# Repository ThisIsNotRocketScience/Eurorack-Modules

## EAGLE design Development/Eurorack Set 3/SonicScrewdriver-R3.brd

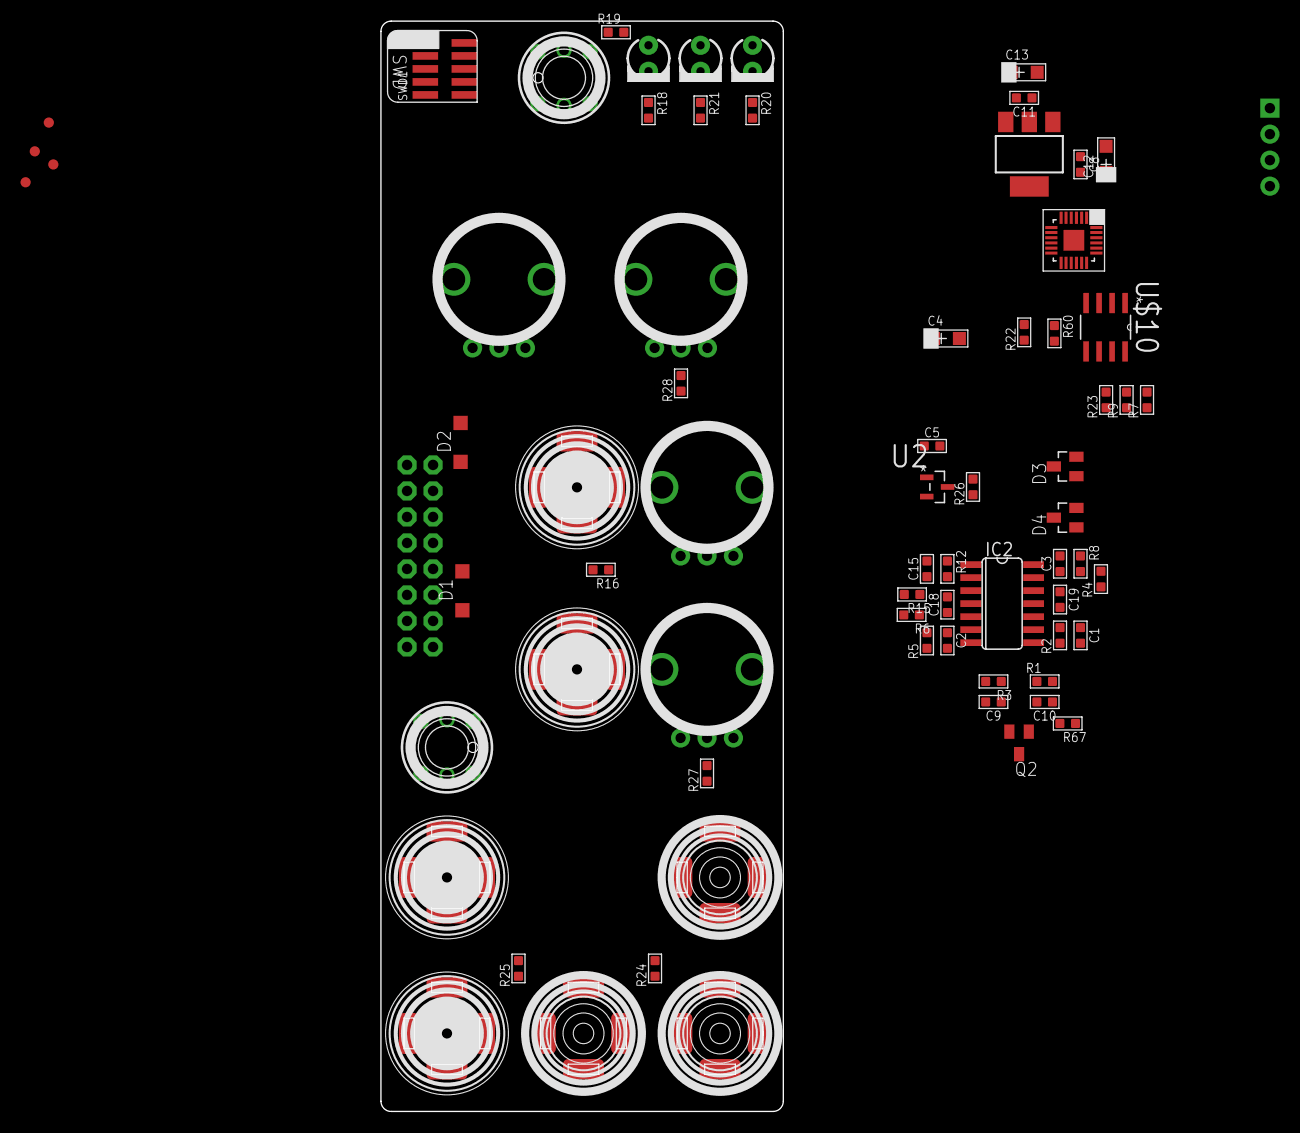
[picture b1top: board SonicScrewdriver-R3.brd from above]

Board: 2 copper layers, 39.3 x 106.5 mm, 73 parts (1 on the bottom side), 49 nets, no tracks yet.

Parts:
C1, C2, C3, C15: 3.3n; C0603
C4, C12: 10uF; AVX-A
C5, C9: 1uF; C0603
C8, C10, C18, C19: 100nF; C0603
C11: 100Nf; C0603
C13: 10Uf; AVX-A
D1, D2: 1N5819HW; SOD123
D3, D4: BAS70-04; SOT23
GATE, GATE1: Gate; 3.5MM-JACK-SWITCH-13MM-INPUT
IC1: LD1117AS33TR; SOT223
IC2: MCP6004; SO14
IN1: In 2; 3.5MM-JACK-SWITCH-13MM-INPUT
IN2: In 1; 3.5MM-JACK-SWITCH-13MM-INPUT
JP1: 1X04
LED1, LED2, LED3: LED3MM
Q2: MMBT3904; SOT23-BEC
R1, R3, R4, R5, R6, R8, R15, R16, R26, R27, R28, R67: 100k; R0603
R2, R7, R9, R12: 33k; R0603
R13: A; OG-POTS_ALPS_POT_VERTICAL
R14: D; OG-POTS_ALPS_POT_VERTICAL
R17: B; OG-POTS_ALPS_POT_VERTICAL
R18, R20, R21: 2k; R0603
R19, R22: 56; R0603
R23, R60: 10k; R0603
R24, R25: 51; R0603
R90: C; OG-POTS_ALPS_POT_VERTICAL
SWD1: CORTEX_SWD; M50-3600542
U1: MKL02Z32VFK4; QFN50P400X400X100-25N
U2: LM4040DIM3-5.0; SOT95P237X112-3N
U$1: POWER; POWER_16
U$2: EURORACK_PCB8HP; EURORACK8HPPCB
U$3, U$6: SWITCH_W_LED_PB6149L-X-102WHITE; PB6149L
U$4, U$5, U$9, U$11: FIDUCIAL; FIDUCIAL_1MM
U$7: Out 2; 3.5MM-JACK-SWITCH-13MM-OUTPUT
U$8, U$12: Out 1; 3.5MM-JACK-SWITCH-13MM-OUTPUT
U$10: MCP4822-E/SN; SOIC8-N_MC

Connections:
3.3V: C8.2, C9.2, C10.2, C12.+, D3.2, D4.2, IC1.2, IC1.4, JP1.4, R13.P$3, R14.P$3, R17.P$3, R23.2, R60.2, R90.P$3, SWD1.1, U1.3, U$3.LEDPOS, U$10.1
ADC_1: C15.2, D3.3, IC2.1, R12.1, U1.15
ADC_2: C1.2, D4.3, IC2.8, R2.1, U1.16
DACCS: U1.7, U$10.2
DACSCK: U1.12, U$10.3
DACSDI: U1.11, U$10.4
GATE: Q2.C, R60.1, U1.8
GND: C4.+, C5.1, C8.1, C9.1, C10.1, C11.1, C12.-, C13.-, C18.1, C19.1, D3.1, D4.1, GATE.RING@1, GATE.RING@2, IC1.1, IC2.3, IC2.5, IC2.10, IC2.12, IN1.RING@1, IN1.RING@2, IN2.RING@1, IN2.RING@2, JP1.1, Q2.E, R13.P$1, R14.P$1, R17.P$1, R18.2, R19.2, R20.2, R21.2, R90.P$1, SWD1.3, SWD1.5, U1.4, U1.25, U2.1, U$1.3, U$1.4, U$1.5, U$1.6, U$1.7, U$1.8, U$3.3, U$3.4, U$6.3, U$6.4, U$7.RING@1, U$7.RING@2, U$8.RING@1, U$8.RING@2, U$10.5, U$10.7
KNOB_A: R90.P$2, U1.19
KNOB_B: R13.P$2, U1.9
KNOB_C: R14.P$2, R27.2
KNOB_D: R17.P$2, R28.2
LED1: U1.1, U$6.LEDPOS
LED2: LED1.A, U1.20
LED3: LED2.A, U1.14
LED4: LED3.A, U1.13
unnamed: JP1.3, U1.5
unnamed: JP1.2, U1.6
unnamed: IN1.TIP@1, IN1.TIP@2, R16.2
unnamed: C15.1, IC2.2, R12.2, R15.1, R16.1, R27.1
unnamed: SWD1.4, U1.22
unnamed: IN2.TIP@1, IN2.TIP@2, R1.2
unnamed: SWD1.2, U1.24
unnamed: C1.1, IC2.9, R1.1, R2.2, R3.1, R28.1
unnamed: C2.1, IC2.6, R5.2, R6.1, R9.1
unnamed: C3.1, IC2.13, R4.2, R7.1, R8.2
unnamed: R7.2, U$10.8
unnamed: R9.2, U$10.6
unnamed: D1.A, U$1.9, U$1.10
unnamed: R19.1, U$6.LEDNEG
unnamed: LED3.K, R18.1
unnamed: LED2.K, R20.1
unnamed: LED1.K, R21.1
unnamed: C3.2, IC2.14, R8.1, R24.2
unnamed: R22.1, U$3.LEDNEG
unnamed: R25.1, U$8.TIP@1, U$8.TIP@2
unnamed: R24.1, U$7.TIP@1, U$7.TIP@2
unnamed: C2.2, IC2.7, R5.1, R25.2
unnamed: GATE.TIP@1, GATE.TIP@2, R67.1
unnamed: D2.C, U$1.1, U$1.2
unnamed: Q2.B, R67.2
PTA1: SWD1.10, U1.23
RACK_GATE: GATE.SWITCH@1, GATE.SWITCH@2, U$1.15, U$1.16
REF_-5V: C5.2, R3.2, R4.1, R6.2, R15.2, R26.2, U2.2
SW1: U1.2, U$6.1, U$6.2
SW2: R23.1, U1.17, U$3.1, U$3.2
SW2LED: R22.2, U1.18
VEE: C4.-, C19.2, D2.A, IC2.11, R26.1
VIN: C11.2, C13.+, C18.2, D1.C, IC1.3, IC2.4

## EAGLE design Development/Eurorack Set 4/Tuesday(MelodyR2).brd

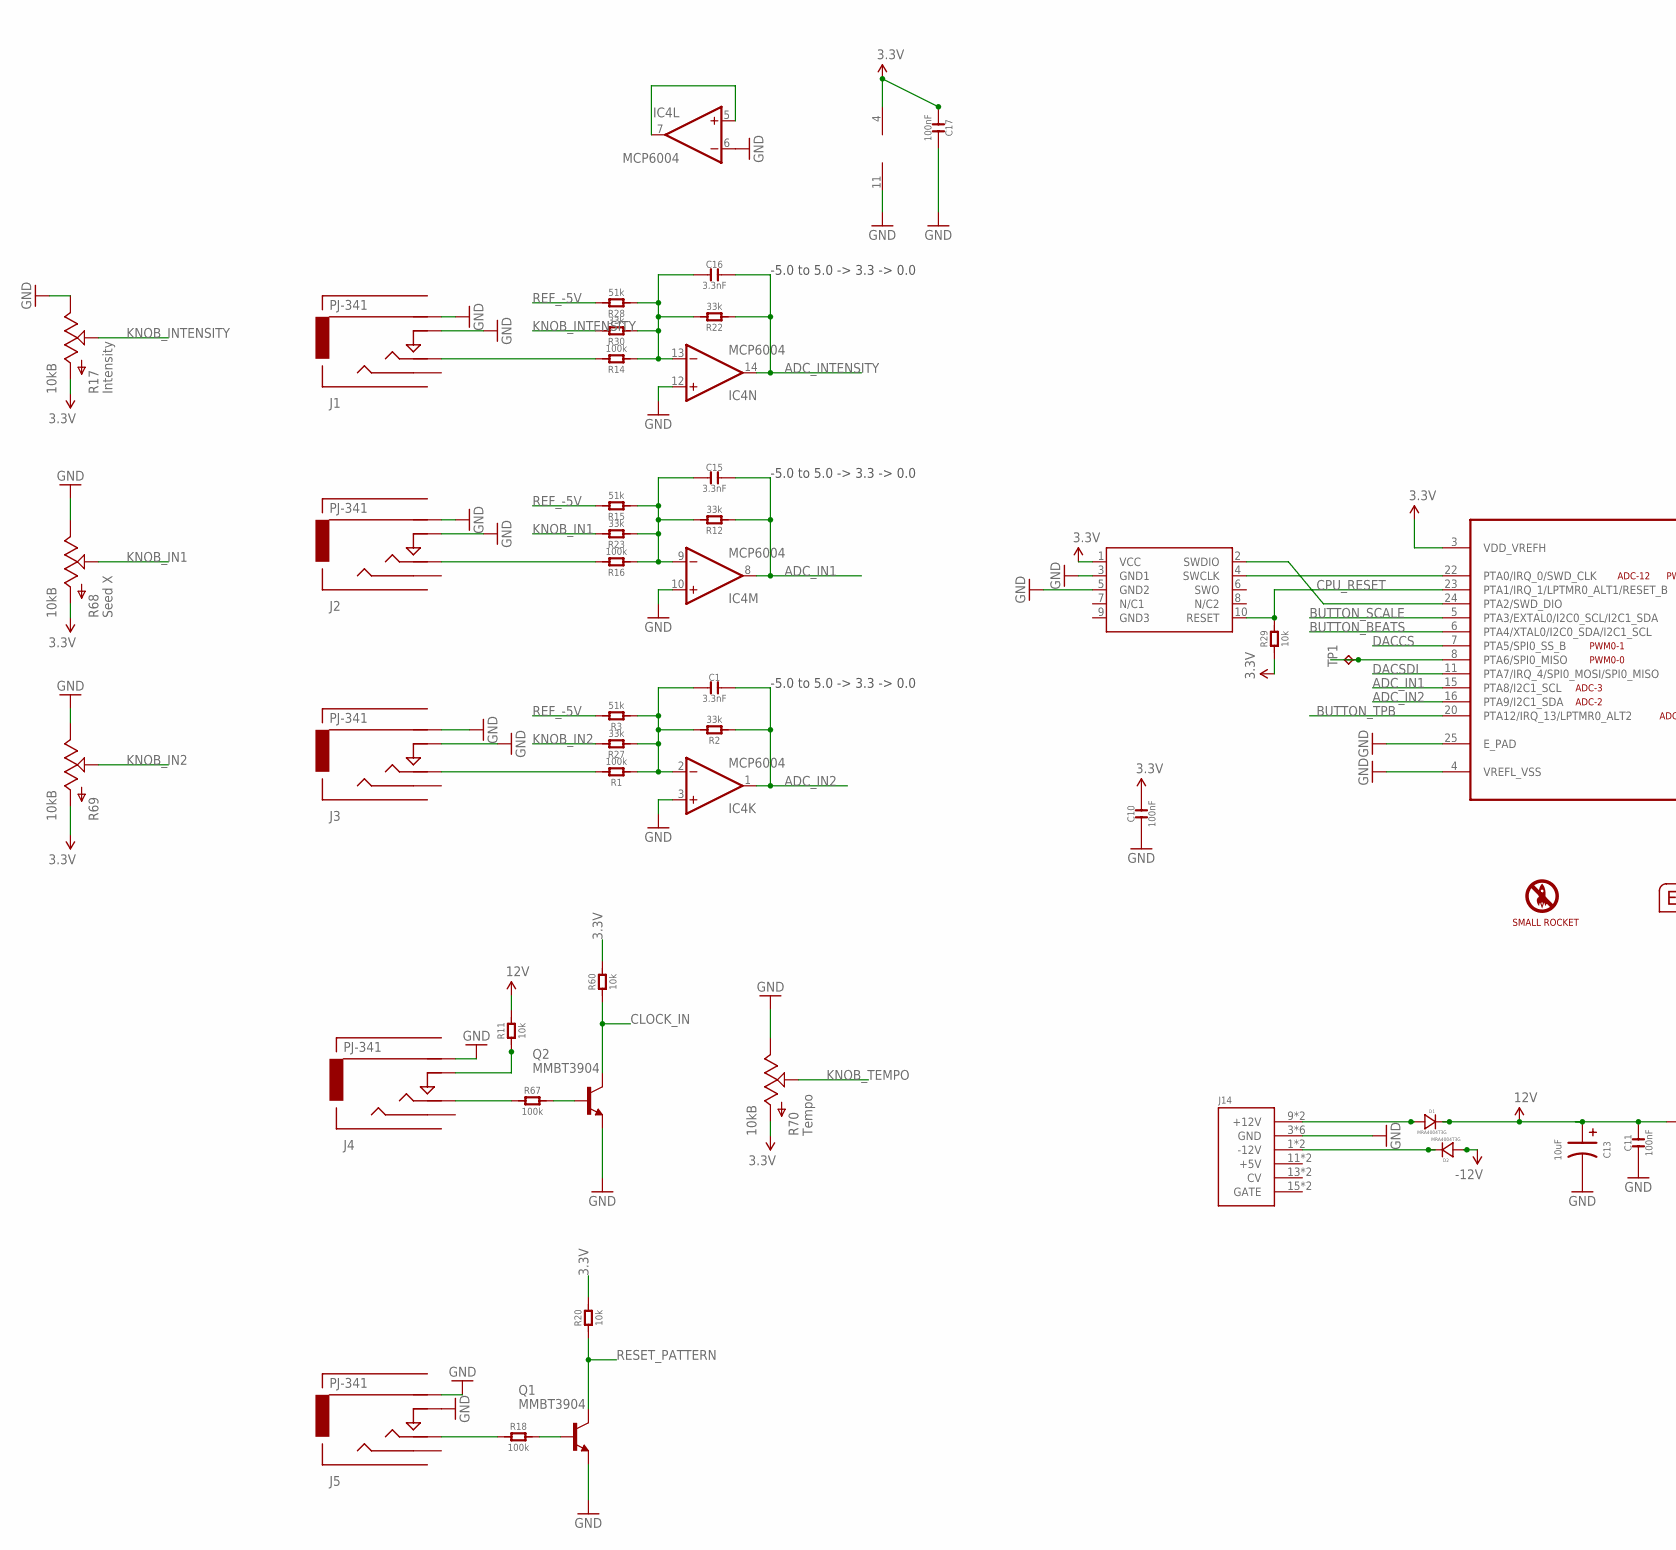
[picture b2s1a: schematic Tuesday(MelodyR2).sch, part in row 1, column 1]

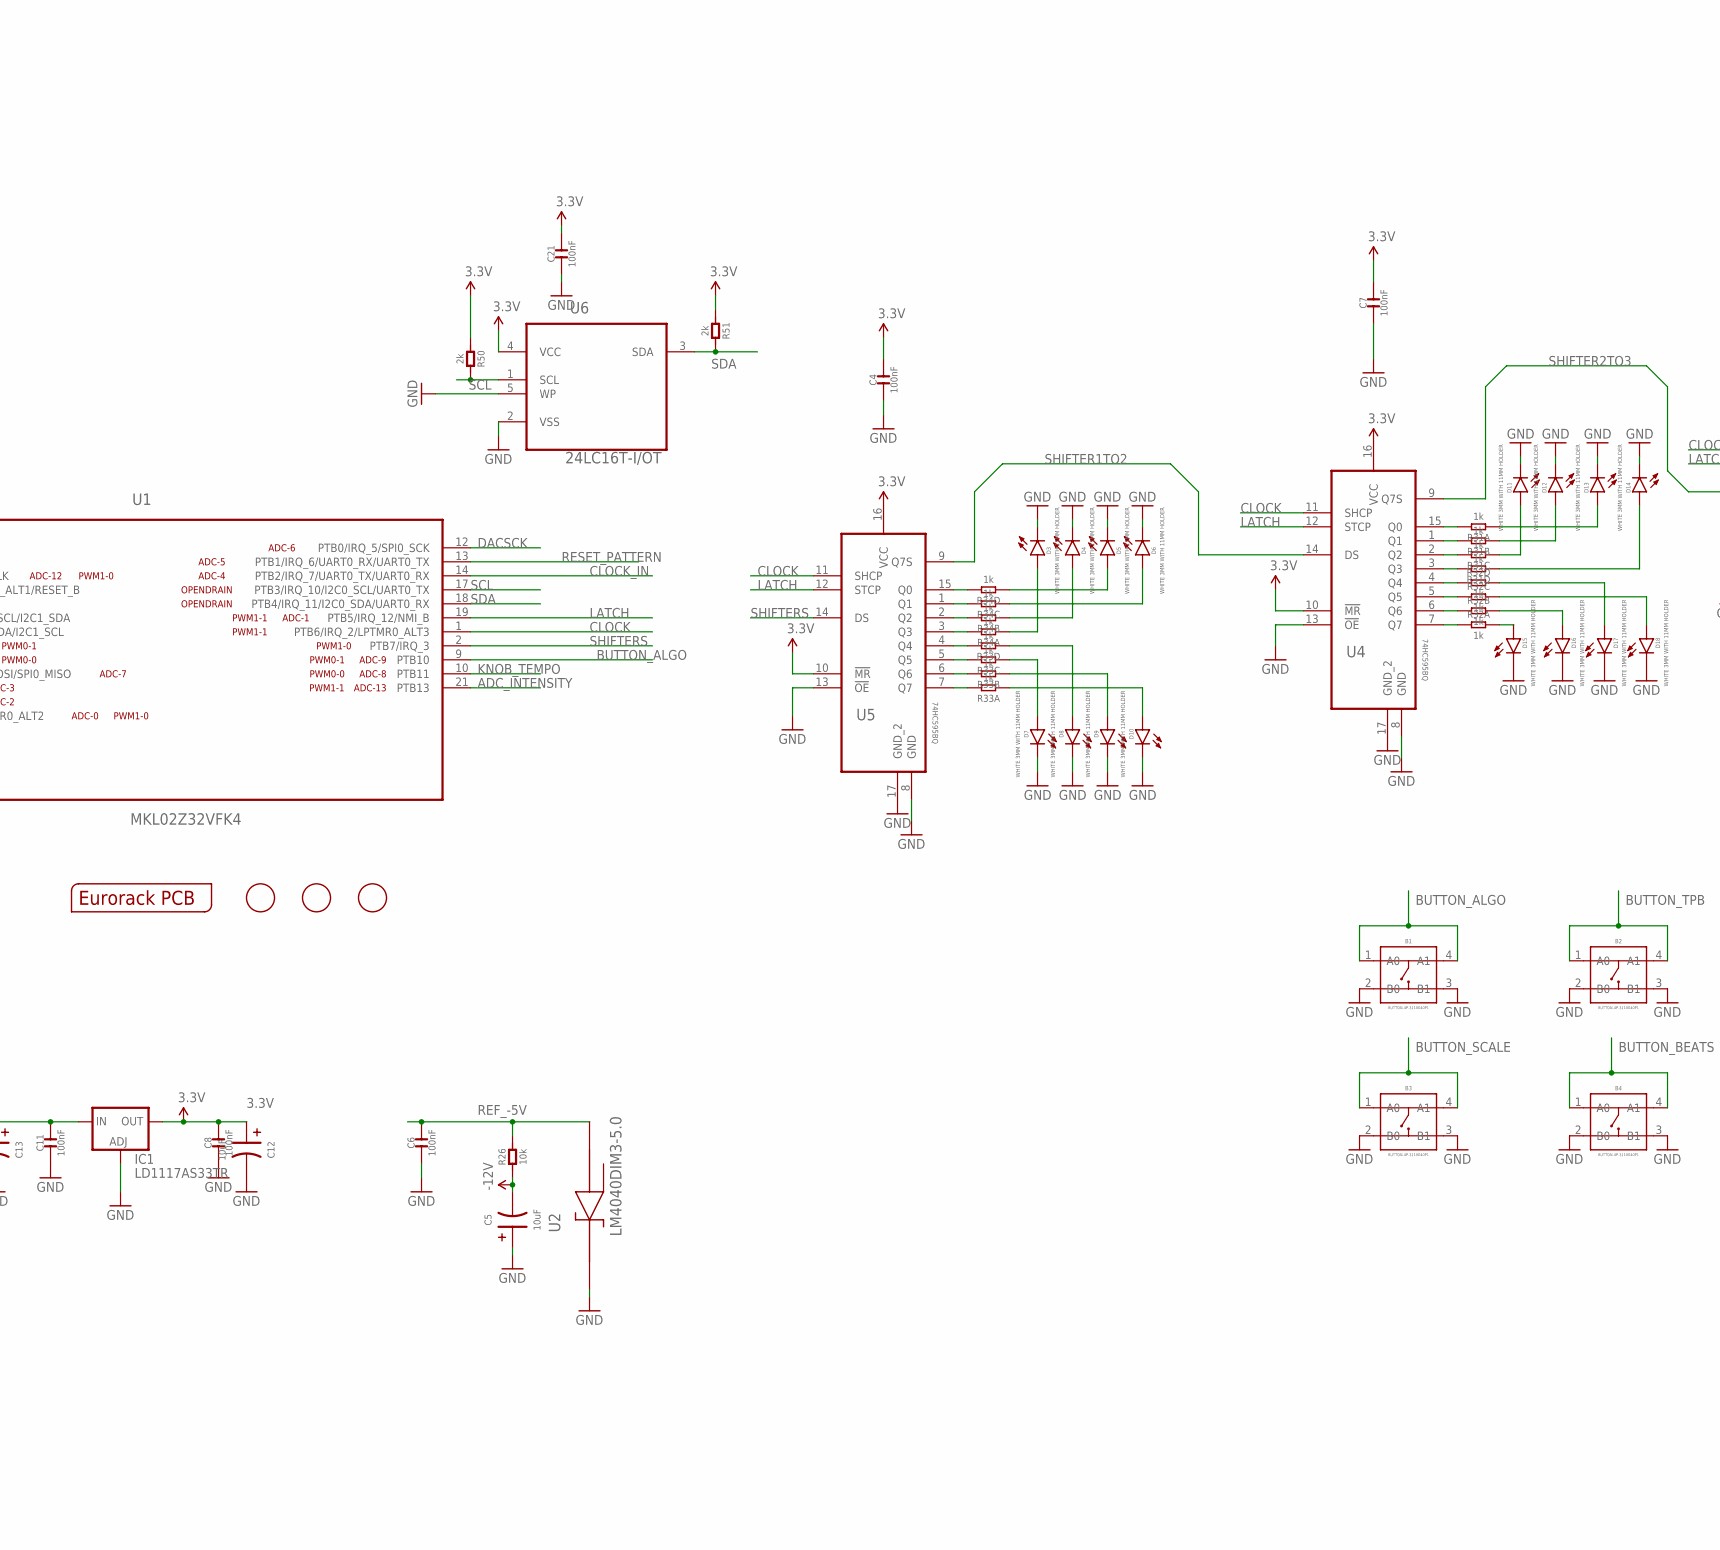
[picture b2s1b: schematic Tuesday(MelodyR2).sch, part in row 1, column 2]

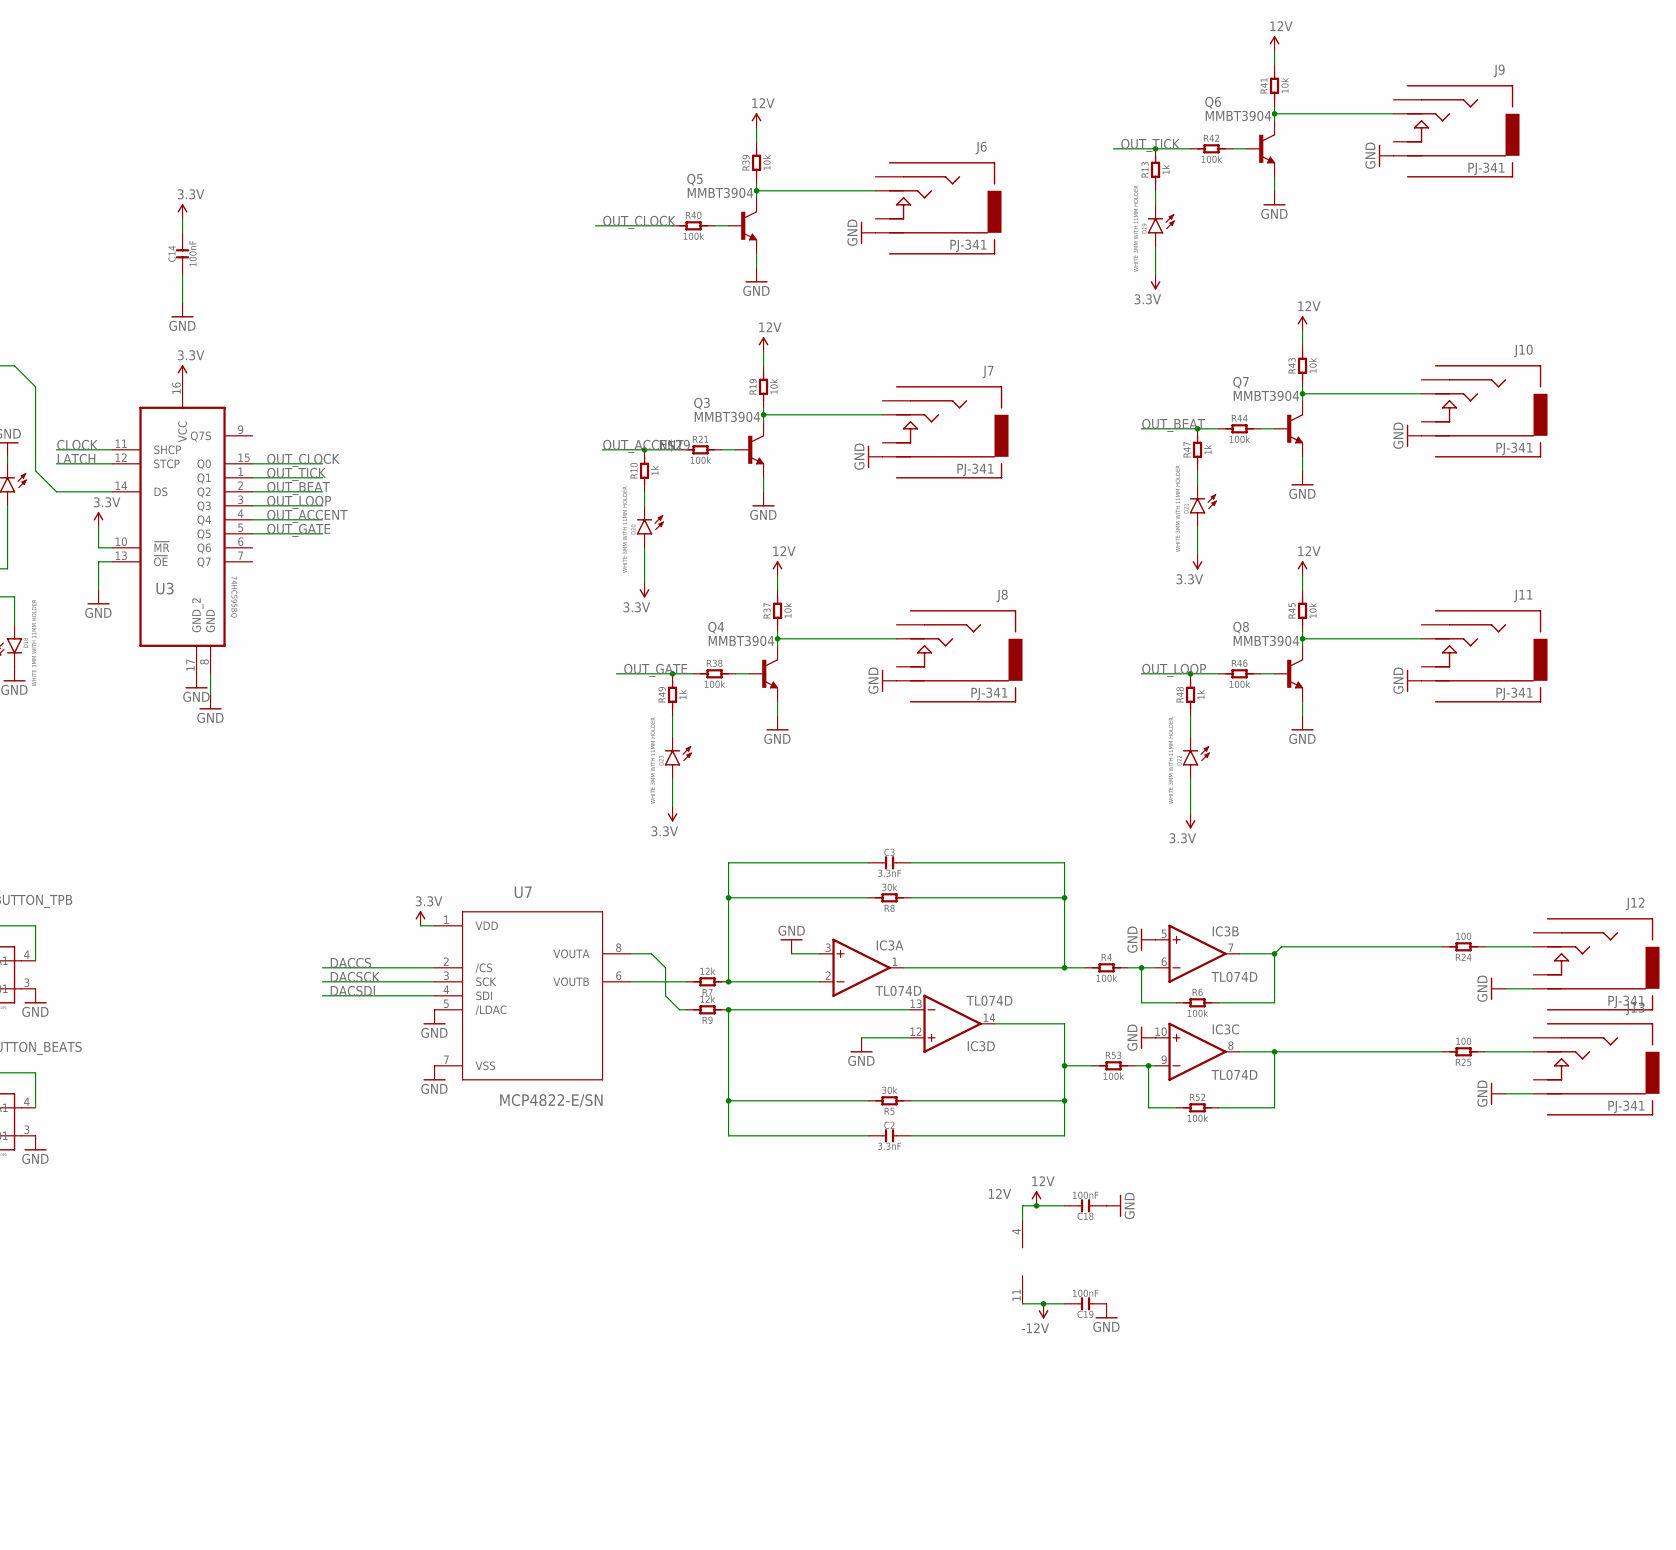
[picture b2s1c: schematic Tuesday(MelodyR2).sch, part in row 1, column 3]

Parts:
B1, B2, B3, B4: BUTTON-4P-3110040P1; 4P-6.0X6.0X5.0H
C1, C2, C3, C15, C16: 3.3nF; C0603
C4, C7, C8, C10, C11, C14, C17, C18, C19, C21: 100nF; C0603; MPN MC0603F104Z160CT
C5, C12, C13: 10uF; AVX-A; MPN TAJB106K020RNJ
C6: 100nF; C0603; MPN 06035C104KAT2A
D1, D2: MRA4004T3G; DO-214AC; MPN US1G-E3/5AT
D3, D4, D5, D6, D7, D8, D9, D10, D11, D12, D13, D14, D15, D16, D17, D18, D19, D20, D21, D22, D23: WHITE 3MM WITH 11MM HOLDER; LED3MM
FID1, FID2, FID3: FIDUCIAL; FIDUCIAL_1MM
IC1: LD1117AS33TR; SOT223; MPN LD1117AS33TR
IC3: TL074D; SO14; MPN TL074CD
IC4: MCP6004; SO14; MPN MCP6004-I/SL.
J1, J2, J3, J4, J5: PJ-341; 3.5MM-JACK-SWITCH-13MM-INPUT
J6, J7, J8, J9, J10, J11, J12, J13: PJ-341; 3.5MM-JACK-SWITCH-13MM-OUTPUT
J14: POWER; POWER_16
OUTLINE: EURORACK_PCB12HP; EURORACK12HPPCB
PRETTY1: SMALLROCKET
Q1, Q2, Q3, Q4, Q5, Q6, Q7, Q8: MMBT3904; SOT23-BEC; MPN PMBT3904,215
R1, R4, R6, R14, R16, R18, R21, R38, R40, R42, R44, R46, R52, R53, R67: 100k; R0603
R2, R12, R22, R23, R27, R30: 33k; R0603
R3, R15, R28: 51k; R0603
R5, R8: 30k; R0603
R7, R9: 12k; R0603
R10, R13, R47, R48, R49: 1k; R0603
R11, R19, R20, R26, R29, R37, R39, R41, R43, R45, R60: 10k; R0603
R17, R68, R69, R70: 10kB; OG-POTS_ALPS_POT_VERTICAL
R24, R25: 100; R0603
R31, R32, R33, R34: 1k; R1206-8
R50, R51: 2k; R0603
SWD1: CORTEX_SWD; M50-3600542
TP1: TPB1,27; B1,27
U1: MKL02Z32VFK4; QFN50P400X400X100-25N
U2: LM4040DIM3-5.0; SOT95P237X112-3N
U3, U4, U5: 74HC595BQ; QFN50P250X350X100-17N
U6: 24LC16T-I/OT; SOT95P290X145-5N; MPN 24LC00T-I/OT
U7: MCP4822-E/SN; SOIC8-N_MC

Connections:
3.3V: C4.2, C7.2, C8.2, C10.2, C12.+ (1), C14.2, C17.1, C21.2, D19.A, D20.A, D21.A, D22.A, D23.A, IC1.2 (OUT), IC1.4 (OUT), IC4.4 (V+), R17.P$3 (A), R20.2, R29.1, R50.1, R51.1, R60.2, R68.P$3 (A), R69.P$3 (A), R70.P$3 (A), SWD1.1 (VCC), U1.3 (VDD_VREFH), U3.10 (!MR), U3.16 (VCC), U4.10 (!MR), U4.16 (VCC), U5.10 (!MR), U5.16 (VCC), U6.4 (VCC), U7.1 (VDD)
12V: C11.2, C13.+ (1), C18.2, D1.2 (-), IC1.3 (IN), IC3.4 (V+), R11.2, R19.2, R37.2, R39.2, R41.2, R43.2, R45.2
-12V: C5.- (2), C19.2, D2.1 (+), IC3.11 (V-), R26.1
ADC_IN1: C15.2, IC4.8 (OUT), R12.1, U1.15 (PTA8/I2C1_SCL)
ADC_IN2: C1.2, IC4.1 (OUT), R2.1, U1.16 (PTA9/I2C1_SDA)
ADC_INTENSITY: C16.2, IC4.14 (OUT), R22.1, U1.21 (PTB13)
BUTTON_ALGO: B1.1 (A0), B1.4 (A1), U1.9 (PTB10)
BUTTON_BEATS: B4.1 (A0), B4.4 (A1), U1.6 (PTA4/XTAL0/I2C0_SDA/I2C1_SCL)
BUTTON_SCALE: B3.1 (A0), B3.4 (A1), U1.5 (PTA3/EXTAL0/I2C0_SCL/I2C1_SDA)
BUTTON_TPB: B2.1 (A0), B2.4 (A1), U1.20 (PTA12/IRQ_13/LPTMR0_ALT2)
CLOCK: U1.1 (PTB6/IRQ_2/LPTMR0_ALT3), U3.11 (SHCP), U4.11 (SHCP), U5.11 (SHCP)
CLOCK_IN: Q2.C, R60.1, U1.14 (PTB2/IRQ_7/UART0_TX/UART0_RX)
CPU_RESET: R29.2, SWD1.10 (RESET), U1.23 (PTA1/IRQ_1/LPTMR0_ALT1/RESET_B)
D21: D21.K (C), R47.1
DACCS: U1.7 (PTA5/SPI0_SS_B), U7.2 (/CS)
DACSCK: U1.12 (PTB0/IRQ_5/SPI0_SCK), U7.3 (SCK)
DACSDI: U1.11 (PTA7/IRQ_4/SPI0_MOSI/SPI0_MISO), U7.4 (SDI)
GND: B1.2 (B0), B1.3 (B1), B2.2 (B0), B2.3 (B1), B3.2 (B0), B3.3 (B1), B4.2 (B0), B4.3 (B1), C4.1, C5.+ (1), C6.1, C7.1, C8.1, C10.1, C11.1, C12.- (2), C13.- (2), C14.1, C17.2, C18.1, C19.1, C21.1, D3.K (C), D4.K (C), D5.K (C), D6.K (C), D7.K (C), D8.K (C), D9.K (C), D10.K (C), D11.K (C), D12.K (C), D13.K (C), D14.K (C), D15.K (C), D16.K (C), D17.K (C), D18.K (C), IC1.1 (ADJ), IC3.3 (+IN), IC3.5 (+IN), IC3.10 (+IN), IC3.12 (+IN), IC4.3 (+IN), IC4.6 (-IN), IC4.10 (+IN), IC4.11 (V-), IC4.12 (+IN), J1.RING@3 (RING), J1.SWITCH@3 (SWITCH), J2.RING@3 (RING), J2.SWITCH@3 (SWITCH), J3.RING@3 (RING), J3.SWITCH@3 (SWITCH), J4.RING@3 (RING), J5.RING@3 (RING), J5.SWITCH@3 (SWITCH), J6.RING@3 (RING), J7.RING@3 (RING), J8.RING@3 (RING), J9.RING@3 (RING), J10.RING@3 (RING), J11.RING@3 (RING), J12.RING@3 (RING), J13.RING@3 (RING), J14.3 (GND), J14.4 (GND), J14.5 (GND), J14.6 (GND), J14.7 (GND), J14.8 (GND), Q1.E, Q2.E, Q3.E, Q4.E, Q5.E, Q6.E, Q7.E, Q8.E, R17.P$1 (E), R68.P$1 (E), R69.P$1 (E), R70.P$1 (E), SWD1.3 (GND1), SWD1.5 (GND2), U1.4 (VREFL_VSS), U1.25 (E_PAD), U2.1 (CATHODE), U3.8 (GND), U3.13 (!OE), U3.17 (GND_2), U4.8 (GND), U4.13 (!OE), U4.17 (GND_2), U5.8 (GND), U5.13 (!OE), U5.17 (GND_2), U6.2 (VSS), U6.5 (WP), U7.5 (/LDAC), U7.7 (VSS)
KNOB_IN1: R23.2, R68.P$2 (S)
KNOB_IN2: R27.2, R69.P$2 (S)
KNOB_INTENSITY: R17.P$2 (S), R30.2
KNOB_TEMPO: R70.P$2 (S), U1.10 (PTB11)
LATCH: U1.19 (PTB5/IRQ_12/NMI_B), U3.12 (STCP), U4.12 (STCP), U5.12 (STCP)
unnamed: R31.7 (2), U4.1 (Q1)
unnamed: IC3.6 (-IN), R4.2, R6.1
unnamed: J2.TIP@3 (TIP), R16.2
unnamed: C15.1, IC4.9 (-IN), R12.2, R15.1, R16.1, R23.1
unnamed: R9.2, U7.8 (VOUTA)
unnamed: J3.TIP@3 (TIP), R1.2
unnamed: R7.2, U7.6 (VOUTB)
unnamed: C1.1, IC4.2 (-IN), R1.1, R2.2, R3.1, R27.1
unnamed: C2.1, IC3.13 (-IN), R5.2, R9.1
unnamed: C3.1, IC3.2 (-IN), R7.1, R8.2
unnamed: D19.K (C), R13.1
unnamed: D1.1 (+), J14.9 (+12V), J14.10 (+12V)
unnamed: IC3.7 (OUT), R6.2, R24.2
unnamed: Q1.B, R18.2
unnamed: J5.TIP@3 (TIP), R18.1
unnamed: IC3.9 (-IN), R52.1, R53.2
unnamed: C3.2, IC3.1 (OUT), R4.1, R8.1
unnamed: R31.6 (2), U4.2 (Q2)
unnamed: J13.TIP@3 (TIP), R25.1
unnamed: J12.TIP@3 (TIP), R24.1
unnamed: D20.K (C), R10.1
unnamed: C2.2, IC3.14 (OUT), R5.1, R53.1
unnamed: Q3.B, R21.2
unnamed: R31.5 (2), U4.3 (Q3)
unnamed: R32.4 (1), U4.4 (Q4)
unnamed: D7.A, R33.6 (2)
unnamed: J7.TIP@3 (TIP), Q3.C, R19.1
unnamed: R32.3 (1), U4.5 (Q5)
unnamed: R32.2 (1), U4.6 (Q6)
unnamed: D8.A, R33.5 (2)
unnamed: J1.TIP@3 (TIP), R14.2
unnamed: C16.1, IC4.13 (-IN), R14.1, R22.2, R28.1, R30.1
unnamed: R32.1, U4.7 (Q7)
unnamed: R31.8 (2), U4.15 (Q0)
unnamed: R34.4 (1), U5.15 (Q0)
unnamed: R34.3 (1), U5.1 (Q1)
unnamed: R34.2 (1), U5.2 (Q2)
unnamed: R34.1, U5.3 (Q3)
unnamed: R33.4 (1), U5.4 (Q4)
unnamed: R33.3 (1), U5.5 (Q5)
unnamed: J4.TIP@3 (TIP), R67.1
unnamed: D23.K (C), R49.1
unnamed: D22.K (C), R48.1
unnamed: R33.2 (1), U5.6 (Q6)
unnamed: R33.1, U5.7 (Q7)
unnamed: Q4.B, R38.2
unnamed: J8.TIP@3 (TIP), Q4.C, R37.1
unnamed: Q5.B, R40.2
unnamed: J6.TIP@3 (TIP), Q5.C, R39.1
unnamed: Q6.B, R42.2
unnamed: D2.2 (-), J14.1 (-12V), J14.2 (-12V)
unnamed: J9.TIP@3 (TIP), Q6.C, R41.1
unnamed: Q2.B, R67.2
unnamed: Q7.B, R44.2
unnamed: J10.TIP@3 (TIP), Q7.C, R43.1
unnamed: Q8.B, R46.2
unnamed: J11.TIP@3 (TIP), Q8.C, R45.1
unnamed: D6.A, R34.6 (2)
unnamed: D5.A, R34.5 (2)
unnamed: D4.A, R34.7 (2)
unnamed: D3.A, R34.8 (2)
unnamed: D9.A, R33.7 (2)
unnamed: D10.A, R33.8 (2)
unnamed: D11.A, R31.3 (1)
unnamed: D12.A, R31.2 (1)
unnamed: D13.A, R31.1
unnamed: D14.A, R31.4 (1)
unnamed: D15.A, R32.8 (2)
unnamed: D16.A, R32.7 (2)
unnamed: D17.A, R32.5 (2)
unnamed: D18.A, R32.6 (2)
unnamed: IC3.8 (OUT), R25.2, R52.2
unnamed: J4.SWITCH@3 (SWITCH), R11.1
unnamed: IC4.5 (+IN), IC4.7 (OUT)
OUT_ACCENT: R10.2, R21.1, U3.4 (Q4)
OUT_BEAT: R44.1, R47.2, U3.2 (Q2)
OUT_CLOCK: R40.1, U3.15 (Q0)
OUT_GATE: R38.1, R49.2, U3.5 (Q5)
OUT_LOOP: R46.1, R48.2, U3.3 (Q3)
OUT_TICK: R13.2, R42.1, U3.1 (Q1)
PTA6: TP1.TP, U1.8 (PTA6/SPI0_MISO)
REF_-5V: C6.2, R3.2, R15.2, R26.2, R28.2, U2.2 (ANODE)
RESET_PATTERN: Q1.C, R20.1, U1.13 (PTB1/IRQ_6/UART0_RX/UART0_TX)
SCL: R50.2, U1.17 (PTB3/IRQ_10/I2C0_SCL/UART0_TX), U6.1 (SCL)
SDA: R51.2, U1.18 (PTB4/IRQ_11/I2C0_SDA/UART0_RX), U6.3 (SDA)
SHIFTER1TO2: U4.14 (DS), U5.9 (Q7S)
SHIFTER2TO3: U3.14 (DS), U4.9 (Q7S)
SHIFTERS: U1.2 (PTB7/IRQ_3), U5.14 (DS)
SWD_CLK: SWD1.4 (SWCLK), U1.22 (PTA0/IRQ_0/SWD_CLK)
SWD_DIO: SWD1.2 (SWDIO), U1.24 (PTA2/SWD_DIO)

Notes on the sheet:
-5.0 to 5.0 -> 3.3 -> 0.0

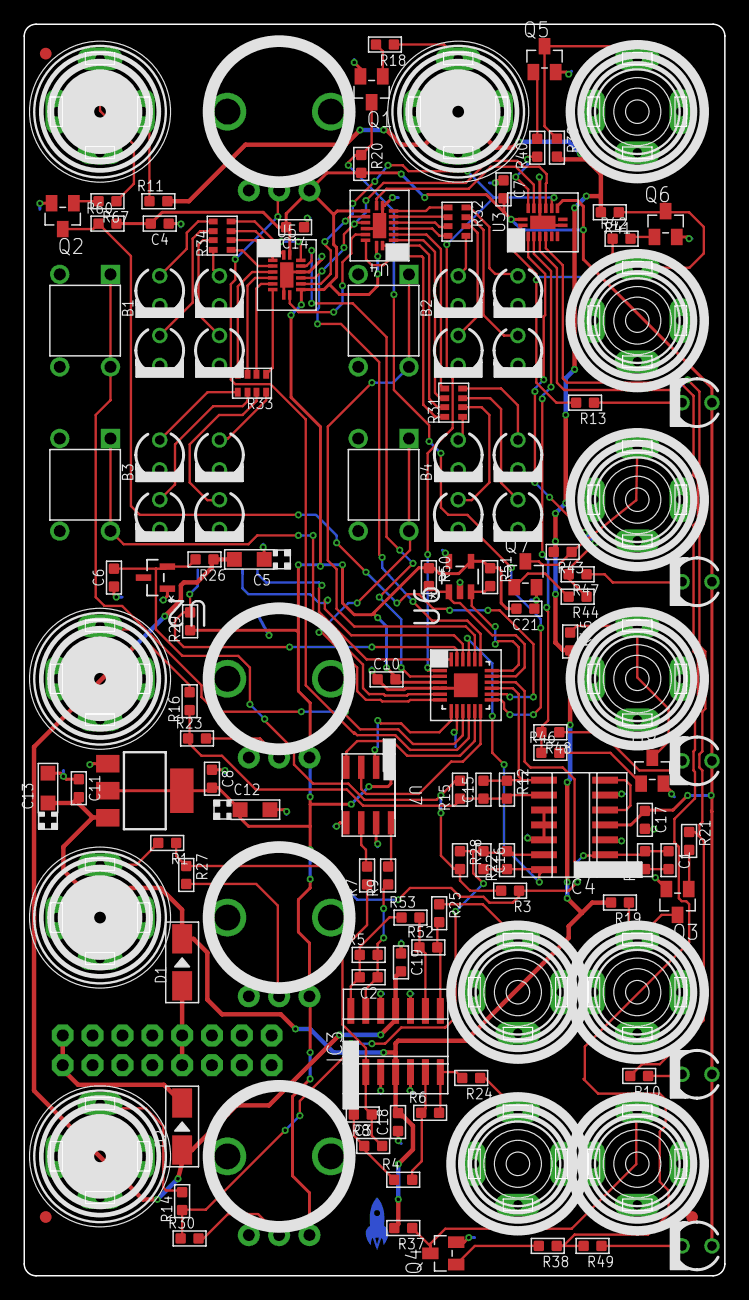
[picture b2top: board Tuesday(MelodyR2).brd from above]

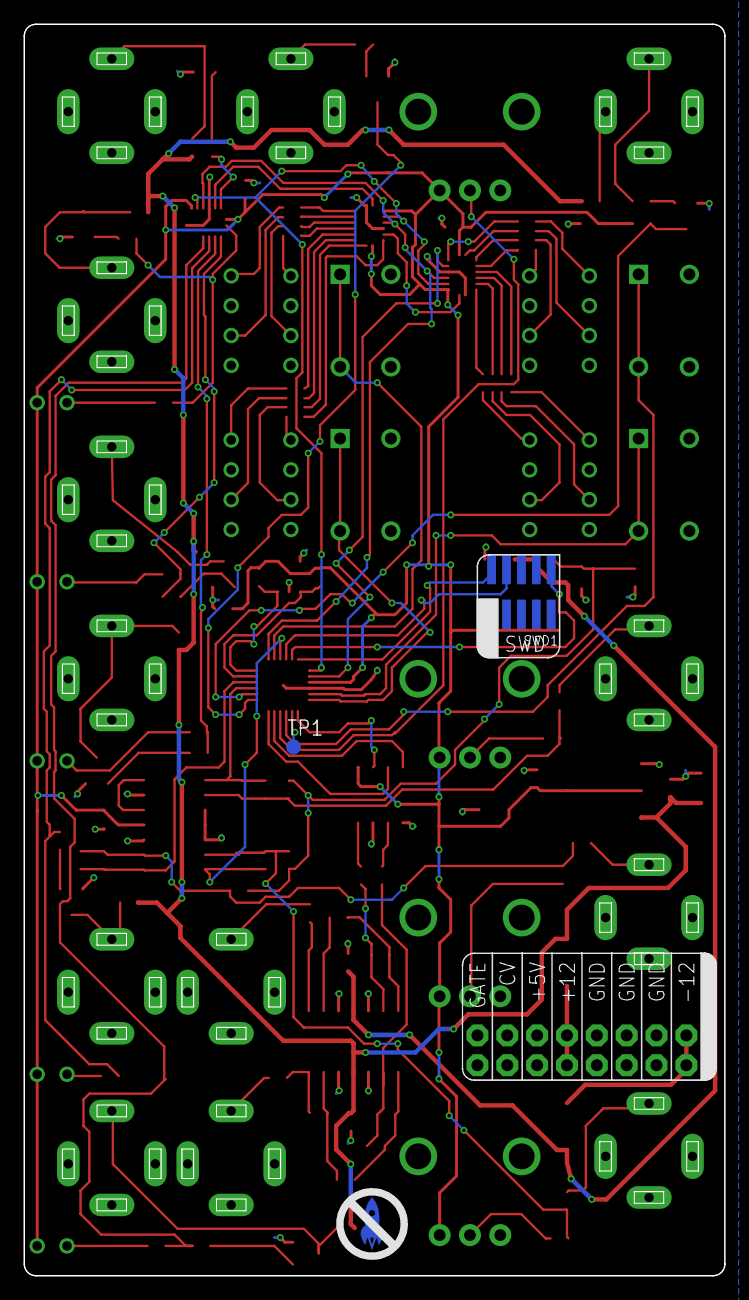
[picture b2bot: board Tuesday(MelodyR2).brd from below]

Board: 2 copper layers, 59.6 x 106.5 mm, 141 parts (4 on the bottom side), 113 nets.

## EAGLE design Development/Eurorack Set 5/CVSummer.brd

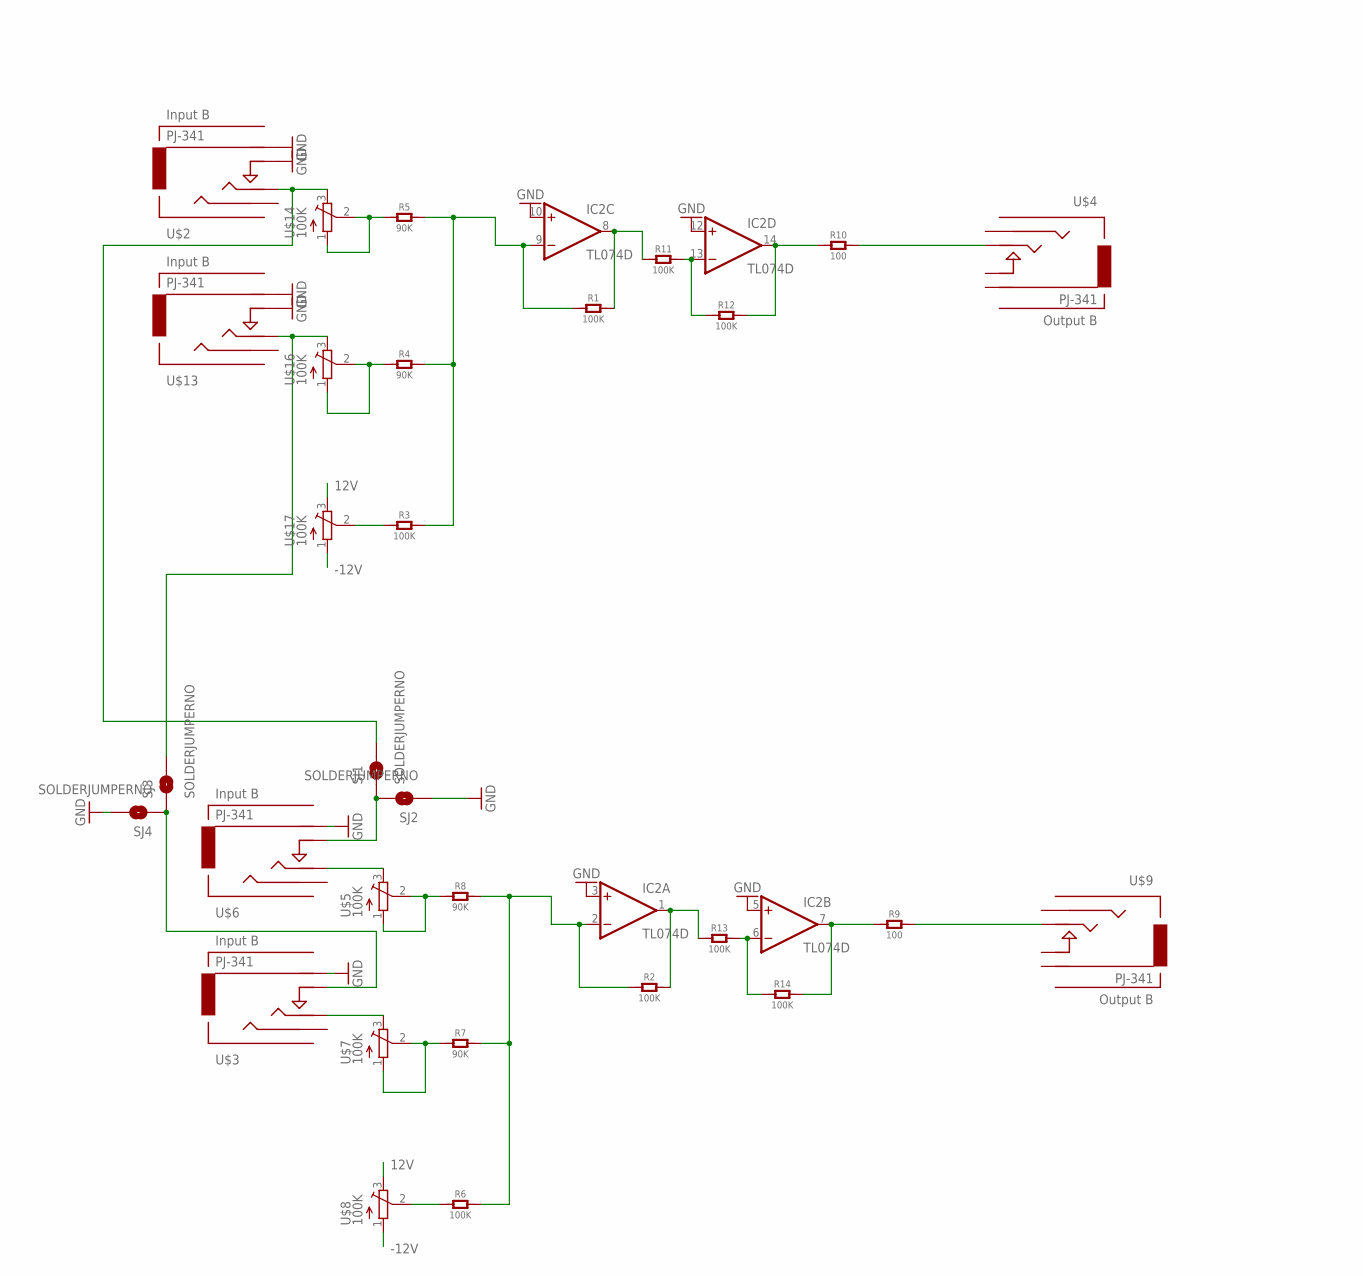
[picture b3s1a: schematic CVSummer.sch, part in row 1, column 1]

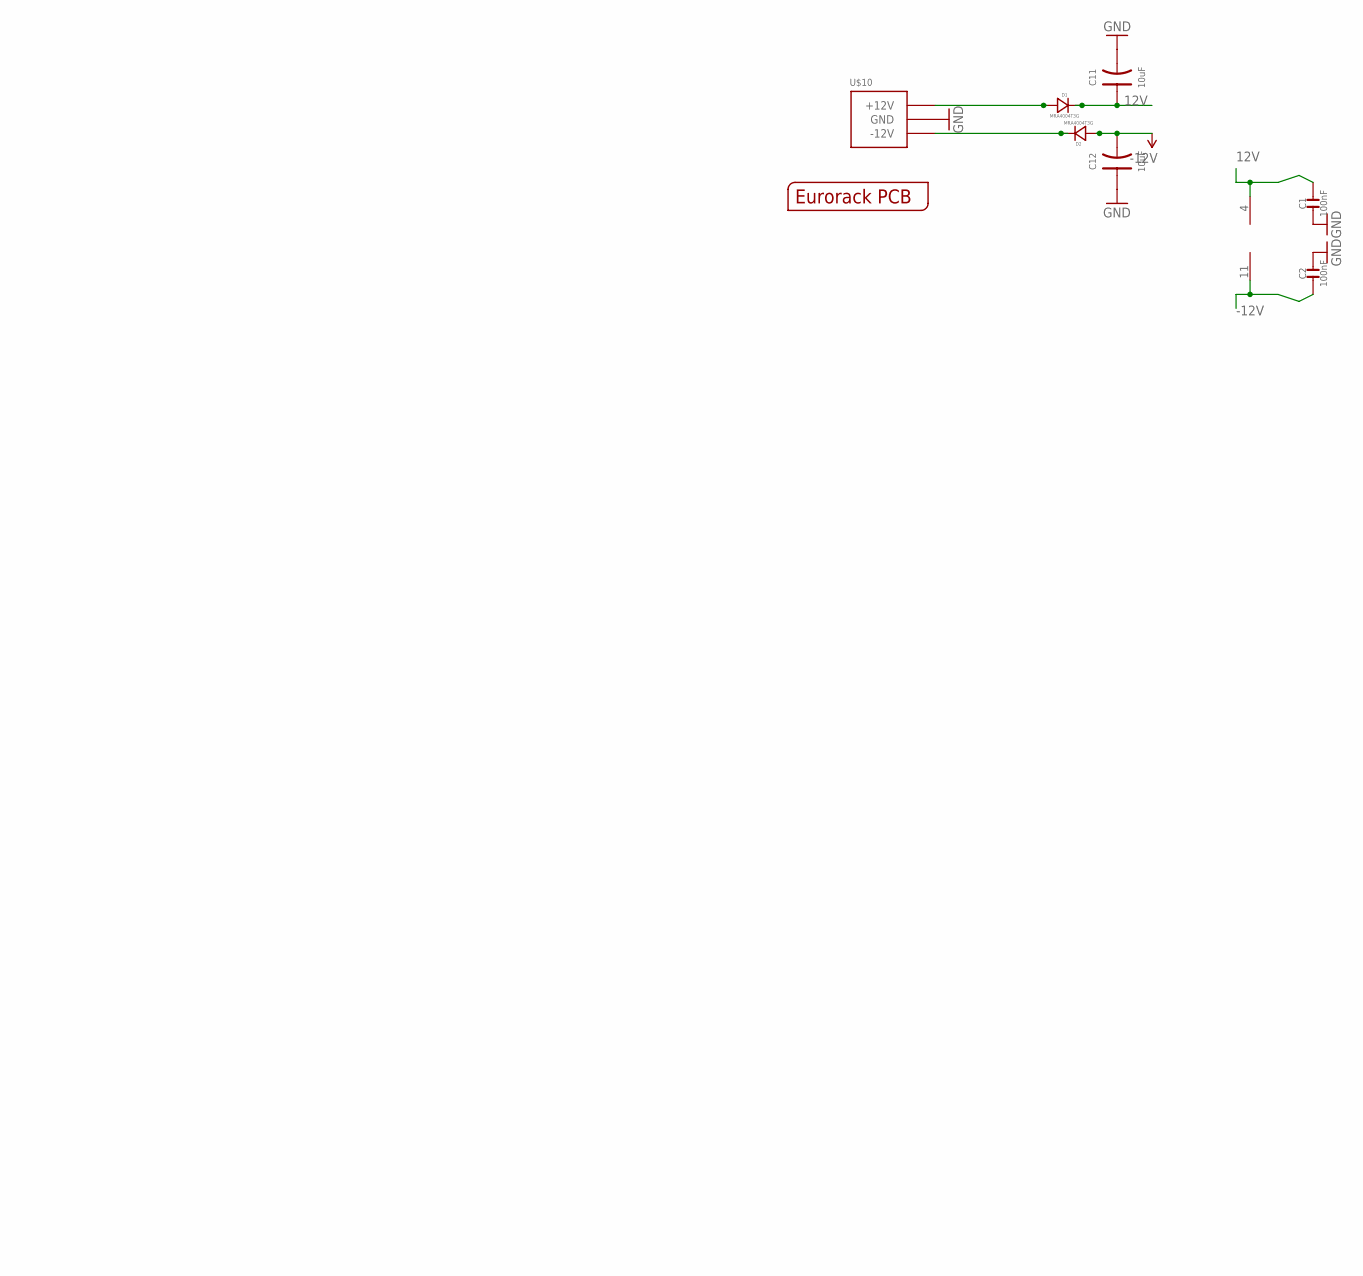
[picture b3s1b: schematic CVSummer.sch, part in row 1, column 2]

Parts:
C1, C2: 100nF; C0603
C11, C12: 10uF; AVX-A
D1, D2: MRA4004T3G; DO-214AC; MPN US1G-E3/5AT
IC2: TL074D; SO14
R1, R2, R3, R6, R11, R12, R13, R14: 100K; C0805
R4, R5, R7, R8: 90K; C0805
R9, R10: 100; C0805
SJ1, SJ2, SJ3, SJ4: SOLDERJUMPERNO; SJ_2S-NO
U$1: EURORACK_PCB4HP; EURORACK4HPPCB
U$2, U$3, U$6, U$13: PJ-341; 3.5MM-JACK-SWITCH-13MM-INPUT
U$4, U$9: PJ-341; 3.5MM-JACK-SWITCH-13MM-OUTPUT
U$5, U$7, U$8, U$14, U$16, U$17: 100K; TC33X
U$10: POWER_SIMPLE10; POWER_10

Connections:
12V: C1.2, C11.+ (1), D1.2 (-), IC2.4 (V+), U$8.3 (E), U$17.3 (E)
-12V: C2.1, C12.- (2), D2.1 (+), IC2.11 (V-), U$8.1 (A), U$17.1 (A)
GND: C1.1, C2.2, C11.- (2), C12.+ (1), IC2.3 (+IN), IC2.5 (+IN), IC2.10 (+IN), IC2.12 (+IN), SJ2.1, SJ4.2, U$2.RING@3 (RING), U$2.SWITCH@3 (SWITCH), U$3.RING@3 (RING), U$6.RING@3 (RING), U$10.3 (GND), U$10.4 (GND), U$10.5 (GND), U$10.6 (GND), U$10.7 (GND), U$10.8 (GND), U$13.RING@3 (RING), U$13.SWITCH@3 (SWITCH)
unnamed: SJ1.1, SJ2.2, U$6.SWITCH@3 (SWITCH)
unnamed: IC2.14 (OUT), R10.1, R12.2
unnamed: R5.1, U$14.1 (A), U$14.2 (S)
unnamed: U$5.3 (E), U$6.TIP@3 (TIP)
unnamed: IC2.7 (OUT), R9.1, R14.2
unnamed: R3.1, U$17.2 (S)
unnamed: IC2.8 (OUT), R1.2, R11.1
unnamed: IC2.13 (-IN), R11.2, R12.1
unnamed: R6.1, U$8.2 (S)
unnamed: R4.1, U$16.1 (A), U$16.2 (S)
unnamed: U$3.TIP@3 (TIP), U$7.3 (E)
unnamed: SJ3.2, U$13.TIP@3 (TIP), U$16.3 (E)
unnamed: IC2.2 (-IN), R2.1, R6.2, R7.2, R8.2
unnamed: IC2.9 (-IN), R1.1, R3.2, R4.2, R5.2
unnamed: R9.2, U$9.TIP@3 (TIP)
unnamed: R8.1, U$5.1 (A), U$5.2 (S)
unnamed: R7.1, U$7.1 (A), U$7.2 (S)
unnamed: IC2.1 (OUT), R2.2, R13.1
unnamed: IC2.6 (-IN), R13.2, R14.1
unnamed: SJ1.2, U$2.TIP@3 (TIP), U$14.3 (E)
unnamed: SJ3.1, SJ4.1, U$3.SWITCH@3 (SWITCH)
unnamed: R10.2, U$4.TIP@3 (TIP)
unnamed: D1.1 (+), U$10.9 (+12V), U$10.10 (+12V)
unnamed: D2.2 (-), U$10.1 (-12V), U$10.2 (-12V)

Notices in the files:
parts and their libraries:
SparkFun-LED: Licensing: CC v3.0 Share-Alike You are welcome to use this library for commercial purposes.
